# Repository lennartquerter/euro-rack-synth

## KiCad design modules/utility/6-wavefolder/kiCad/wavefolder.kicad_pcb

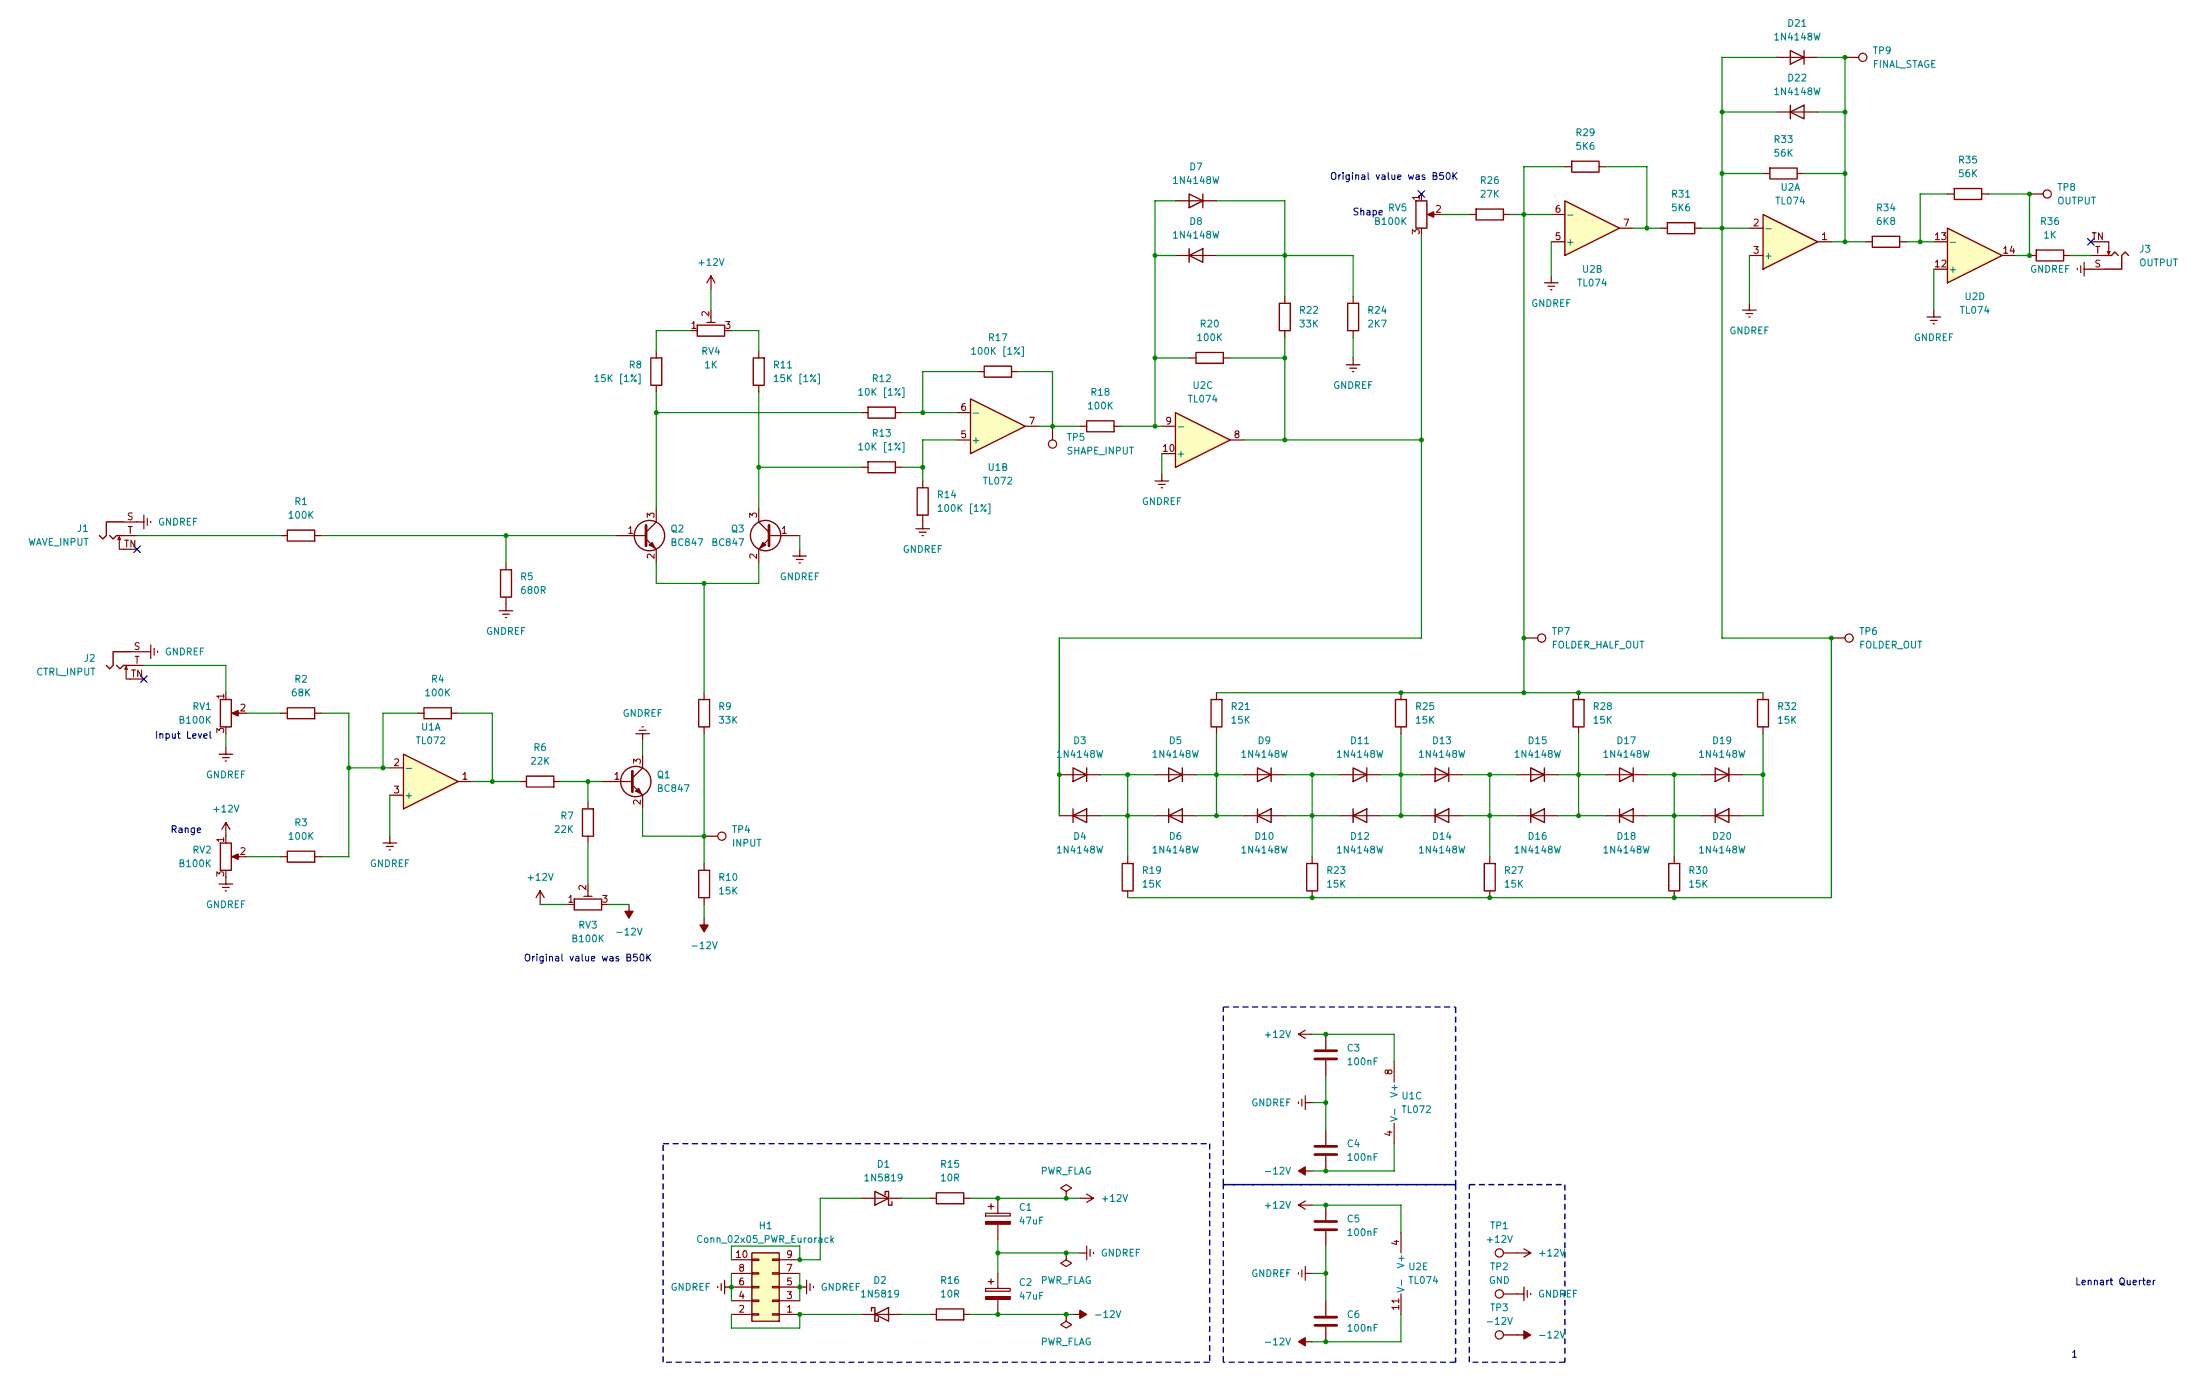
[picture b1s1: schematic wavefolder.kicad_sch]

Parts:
C1, C2: 47uF; CP_Radial_D6.3mm_P2.50mm
C3, C4, C5, C6: 100nF; C_0805_2012Metric_Pad1.18x1.45mm_HandSolder
D1, D2: 1N5819; D_SOD-123
D3, D4, D5, D6, D7, D8, D9, D10, D11, D12, D13, D14, D15, D16, D17, D18, D19, D20, D21, D22: 1N4148W; D_SOD-123
H1: Conn_02x05_PWR_Eurorack; IDC-Header_2x05_P2.54mm_Vertical
J1: WAVE_INPUT; Jack_3.5mm_QingPu_WQP-PJ398SM_Vertical_CircularHoles
J2: CTRL_INPUT; Jack_3.5mm_QingPu_WQP-PJ398SM_Vertical_CircularHoles
J3: OUTPUT; Jack_3.5mm_QingPu_WQP-PJ398SM_Vertical_CircularHoles
Q1, Q2, Q3: BC847; SOT-23
R1, R3, R4, R18, R20: 100K; R_0805_2012Metric_Pad1.20x1.40mm_HandSolder
R2: 68K; R_0805_2012Metric_Pad1.20x1.40mm_HandSolder
R5: 680R; R_0805_2012Metric_Pad1.20x1.40mm_HandSolder
R6, R7: 22K; R_0805_2012Metric_Pad1.20x1.40mm_HandSolder
R8, R11: 15K [1%]; R_0805_2012Metric_Pad1.20x1.40mm_HandSolder
R9, R22: 33K; R_0805_2012Metric_Pad1.20x1.40mm_HandSolder
R10, R19, R21, R23, R25, R27, R28, R30, R32: 15K; R_0805_2012Metric_Pad1.20x1.40mm_HandSolder
R12, R13: 10K [1%]; R_0805_2012Metric_Pad1.20x1.40mm_HandSolder
R14, R17: 100K [1%]; R_0805_2012Metric_Pad1.20x1.40mm_HandSolder
R15, R16: 10R; R_0805_2012Metric_Pad1.20x1.40mm_HandSolder
R24: 2K7; R_0805_2012Metric_Pad1.20x1.40mm_HandSolder
R26: 27K; R_0805_2012Metric_Pad1.20x1.40mm_HandSolder
R29, R31: 5K6; R_0805_2012Metric_Pad1.20x1.40mm_HandSolder
R33, R35: 56K; R_0805_2012Metric_Pad1.20x1.40mm_HandSolder
R34: 6K8; R_0805_2012Metric_Pad1.20x1.40mm_HandSolder
R36: 1K; R_0805_2012Metric_Pad1.20x1.40mm_HandSolder
RV1, RV2, RV5: B100K; Potentiometer_TT_P0915N
RV3: B100K; Potentiometer_Bourns_3296W_Vertical
RV4: 1K; Potentiometer_Bourns_3296W_Vertical
TP1: +12V; Pin_D1.0mm_L10.0mm
TP2: GND; Pin_D1.0mm_L10.0mm
TP3: -12V; Pin_D1.0mm_L10.0mm
TP4: INPUT; Pin_D1.0mm_L10.0mm
TP5: SHAPE_INPUT; Pin_D1.0mm_L10.0mm
TP6: FOLDER_OUT; Pin_D1.0mm_L10.0mm
TP7: FOLDER_HALF_OUT; Pin_D1.0mm_L10.0mm
TP8: OUTPUT; Pin_D1.0mm_L10.0mm
TP9: FINAL_STAGE; Pin_D1.0mm_L10.0mm
U1: TL072; SO-8_3.9x4.9mm_P1.27mm
U2: TL074; SO-14_3.9x8.65mm_P1.27mm

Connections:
+12V: C1.1, C3.1, C5.1, R15.2, RV2.1, RV3.1, RV4.2, TP1.1, U1.8 (V+), U2.4 (V+)
-12V: C2.2, C4.2, C6.2, R10.1, R16.2, RV3.3, TP3.1, U1.4 (V-), U2.11 (V-)
GNDREF: C1.2, C2.1, C3.2, C4.1, C5.2, C6.1, H1.3, H1.4, H1.5, H1.6, H1.7, H1.8, J1.S, J2.S, J3.S, Q1.3 (C), Q3.1 (B), R5.1, R14.2, R24.1, RV1.3, RV2.3, TP2.1, U1.3 (+), U2.3 (+), U2.5 (+), U2.10 (+), U2.12 (+)
unnamed: D1.2 (A), H1.9, H1.10
unnamed: D1.1 (K), R15.1
unnamed: D2.2 (A), R16.1
unnamed: D2.1 (K), H1.1, H1.2
unnamed: D3.2 (A), D4.1 (K), R20.2, R22.1, RV5.3, U2.8
unnamed: D3.1 (K), D4.2 (A), D5.2 (A), D6.1 (K), R19.2
unnamed: D7.2 (A), D8.1 (K), R18.2, R20.1, U2.9 (-)
unnamed: D7.1 (K), D8.2 (A), R22.2, R24.2
unnamed: D9.1 (K), D10.2 (A), D11.2 (A), D12.1 (K), R23.2
unnamed: D5.1 (K), D6.2 (A), D9.2 (A), D10.1 (K), R21.1
unnamed: D11.1 (K), D12.2 (A), D13.2 (A), D14.1 (K), R25.1
unnamed: D13.1 (K), D14.2 (A), D15.2 (A), D16.1 (K), R27.2
unnamed: D15.1 (K), D16.2 (A), D17.2 (A), D18.1 (K), R28.1
unnamed: D17.1 (K), D18.2 (A), D19.2 (A), D20.1 (K), R30.2
unnamed: D19.1 (K), D20.2 (A), R32.1
unnamed: D21.2 (A), D22.1 (K), R19.1, R23.1, R27.1, R30.1, R31.1, R33.2, TP6.1, U2.2 (-)
unnamed: D21.1 (K), D22.2 (A), R33.1, R34.2, TP9.1, U2.1
unnamed: J1.T, R1.1
unnamed: J2.T, RV1.1
unnamed: J3.T, R36.1
unnamed: Q1.1 (B), R6.2, R7.2
unnamed: Q1.2 (E), R9.1, R10.2, TP4.1
unnamed: Q2.1 (B), R1.2, R5.2
unnamed: Q2.3 (C), R8.1, R12.2
unnamed: Q2.2 (E), Q3.2 (E), R9.2
unnamed: Q3.3 (C), R11.1, R13.2
unnamed: R2.1, RV1.2
unnamed: R3.1, RV2.2
unnamed: R4.2, R6.1, U1.1
unnamed: R7.1, RV3.2
unnamed: R8.2, RV4.1
unnamed: R11.2, RV4.3
unnamed: R17.2, R18.1, TP5.1, U1.7
unnamed: R26.2, RV5.2
unnamed: R29.1, R31.2, U2.7
unnamed: R35.1, R36.2, TP8.1, U2.14
unnamed: R2.2, R3.2, R4.1, U1.2 (-)
unnamed: R13.1, R14.1, U1.5 (+)
unnamed: R12.1, R17.1, U1.6 (-)
unnamed: R21.2, R25.2, R26.1, R28.2, R29.2, R32.2, TP7.1, U2.6 (-)
unnamed: R34.1, R35.2, U2.13 (-)

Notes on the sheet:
Original value was B50K
Range
Shape
Lennart Querter
Input Level

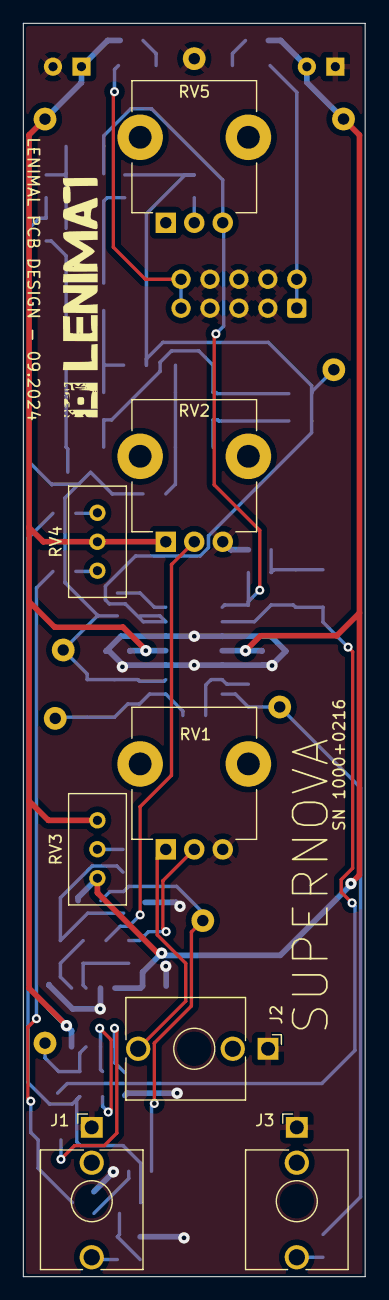
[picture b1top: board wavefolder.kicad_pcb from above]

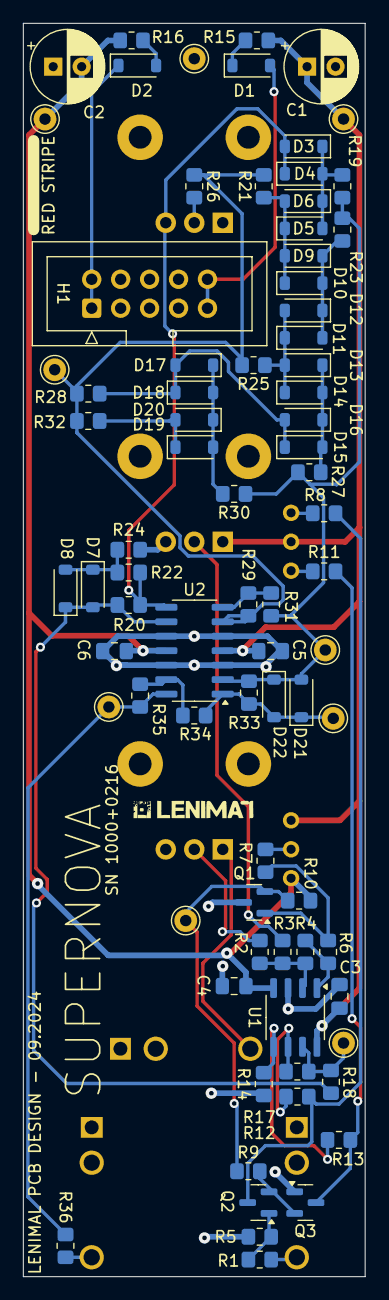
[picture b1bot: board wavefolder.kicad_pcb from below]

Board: 2 copper layers, 30.0 x 110.0 mm, 87 parts (79 on the bottom side), 44 nets.

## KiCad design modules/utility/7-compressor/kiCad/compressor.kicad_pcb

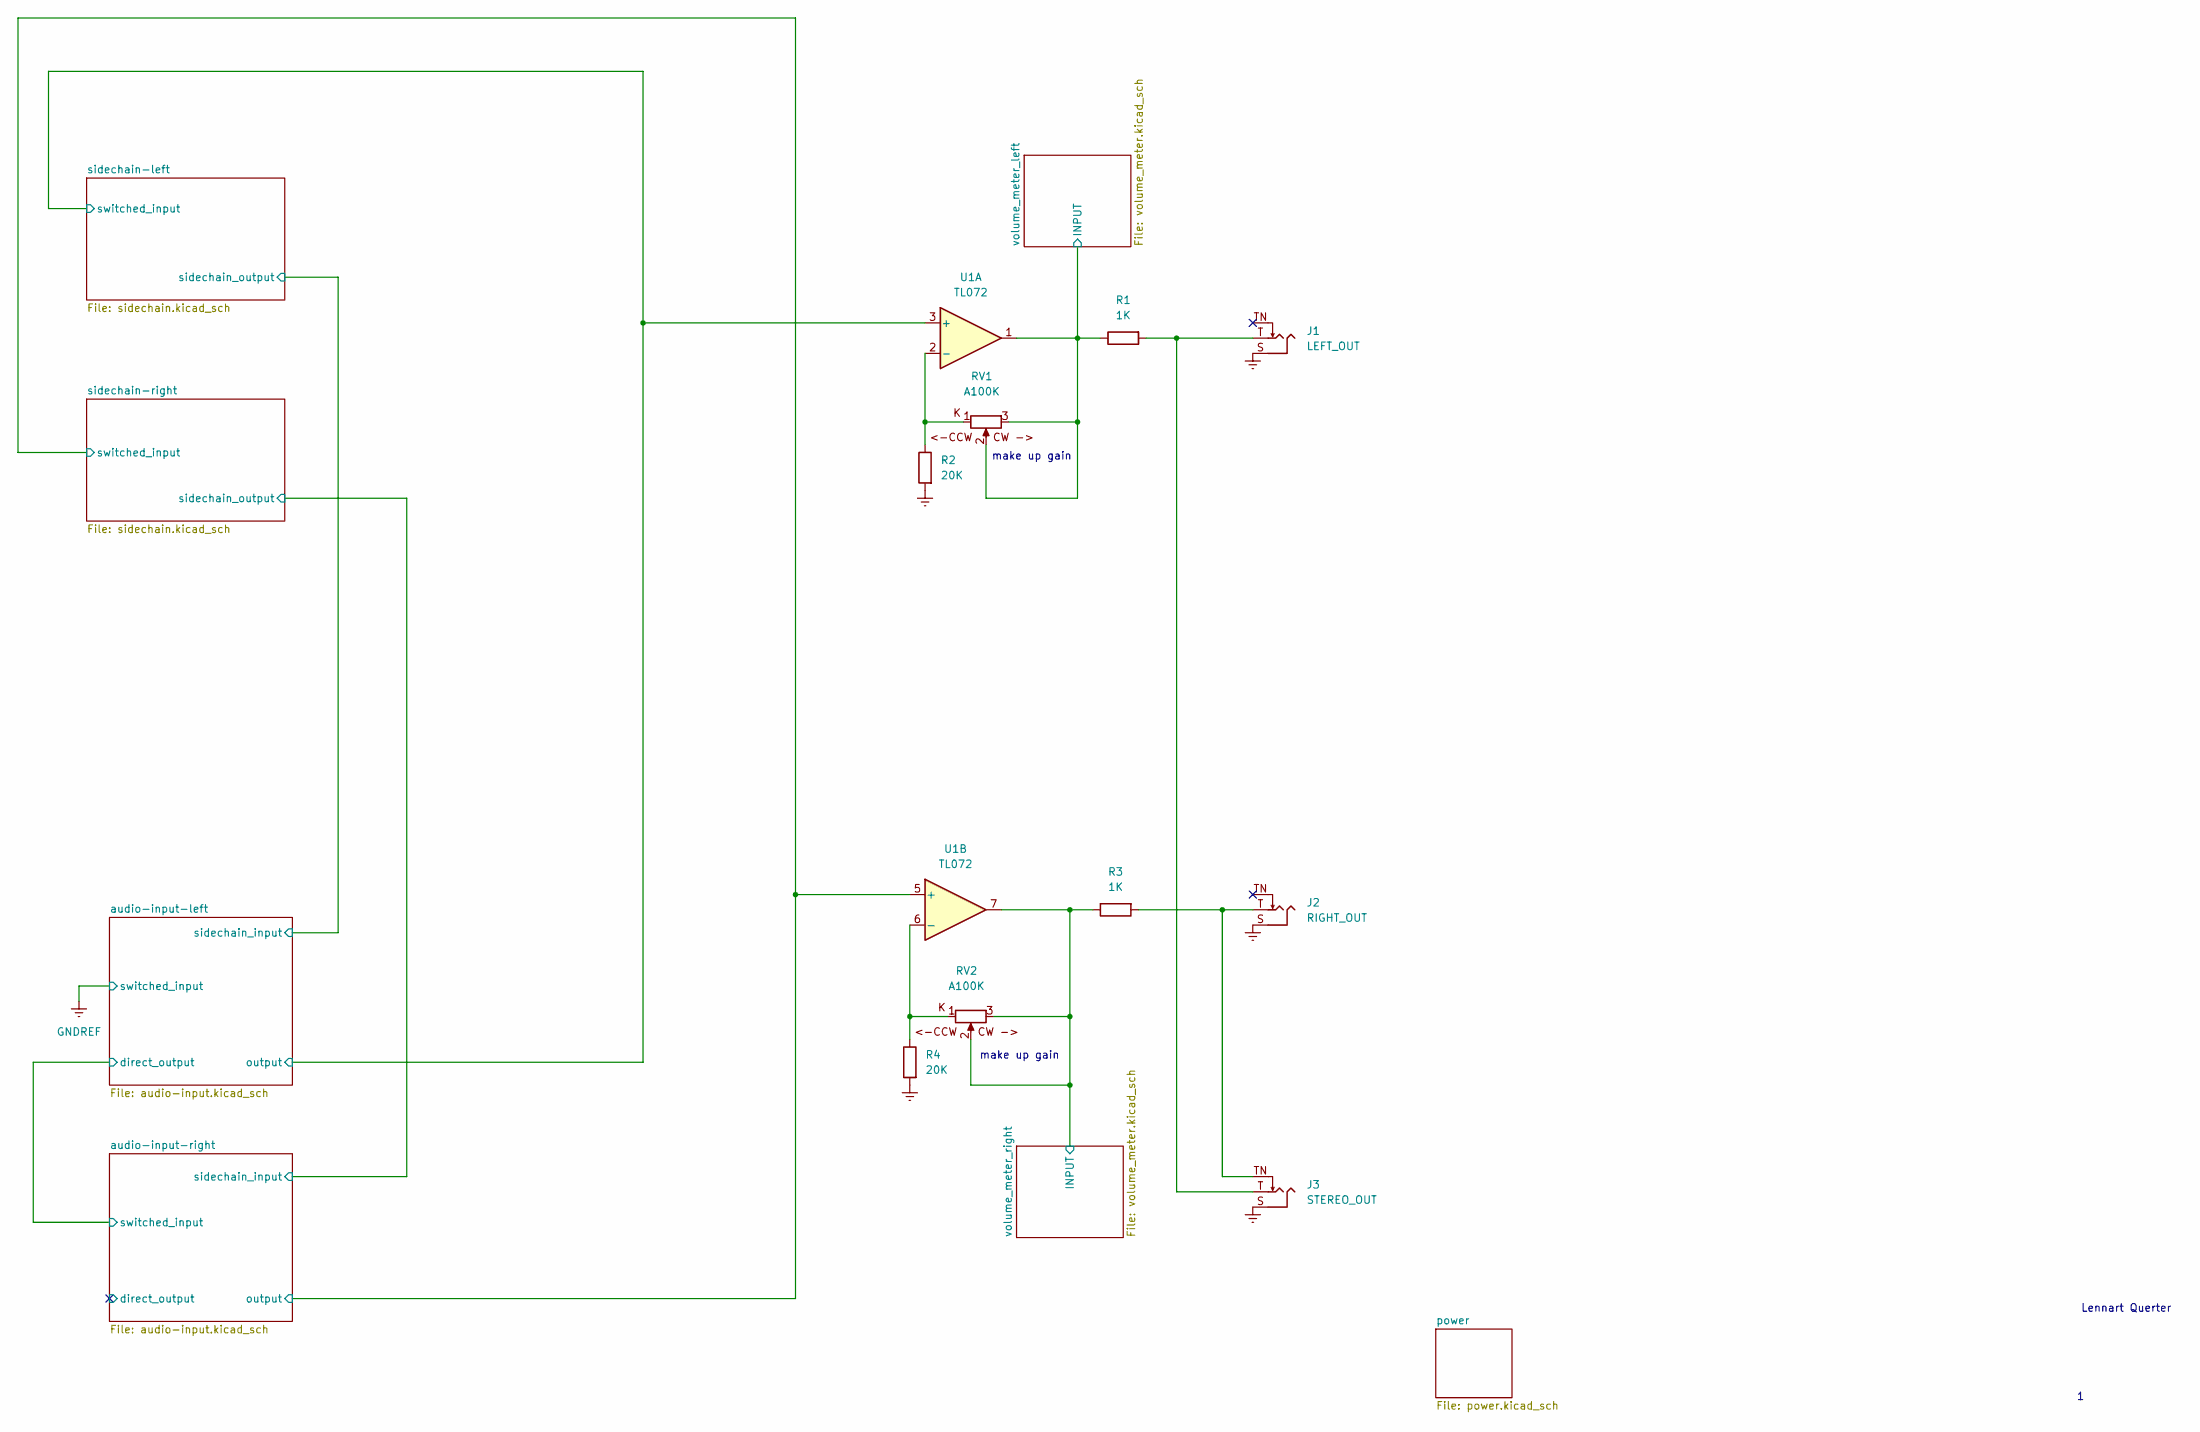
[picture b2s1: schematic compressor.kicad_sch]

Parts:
J1: LEFT_OUT; Jack_3.5mm_QingPu_WQP-PJ398SM_Vertical_CircularHoles
J2: RIGHT_OUT; Jack_3.5mm_QingPu_WQP-PJ398SM_Vertical_CircularHoles
J3: STEREO_OUT; Jack_3.5mm_QingPu_WQP-PJ398SM_Vertical_CircularHoles
R1, R3: 1K; R_0805_2012Metric_Pad1.20x1.40mm_HandSolder
R2, R4: 20K; R_0805_2012Metric_Pad1.20x1.40mm_HandSolder
RV1, RV2: A100K; Potentiometer_TT_P0915N
U1: TL072; SOIC-8

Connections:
/audio-input-left/output: U1.3 (+); also elsewhere on the board
/audio-input-right/output: U1.5 (+); also elsewhere on the board
/volume_meter_left/INPUT: R1.2, RV1.2, RV1.3, U1.1; also elsewhere on the board
/volume_meter_right/INPUT: R3.2, RV2.2, RV2.3, U1.7; also elsewhere on the board
GNDREF: J1.S, J2.S, J3.S, R2.1, R4.1; also elsewhere on the board
unnamed: J1.T, J3.T, R1.1
unnamed: J2.T, J3.TN, R3.1
unnamed: R2.2, RV1.1, U1.2 (-)
unnamed: R4.2, RV2.1, U1.6 (-)

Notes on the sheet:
make up gain
Lennart Querter

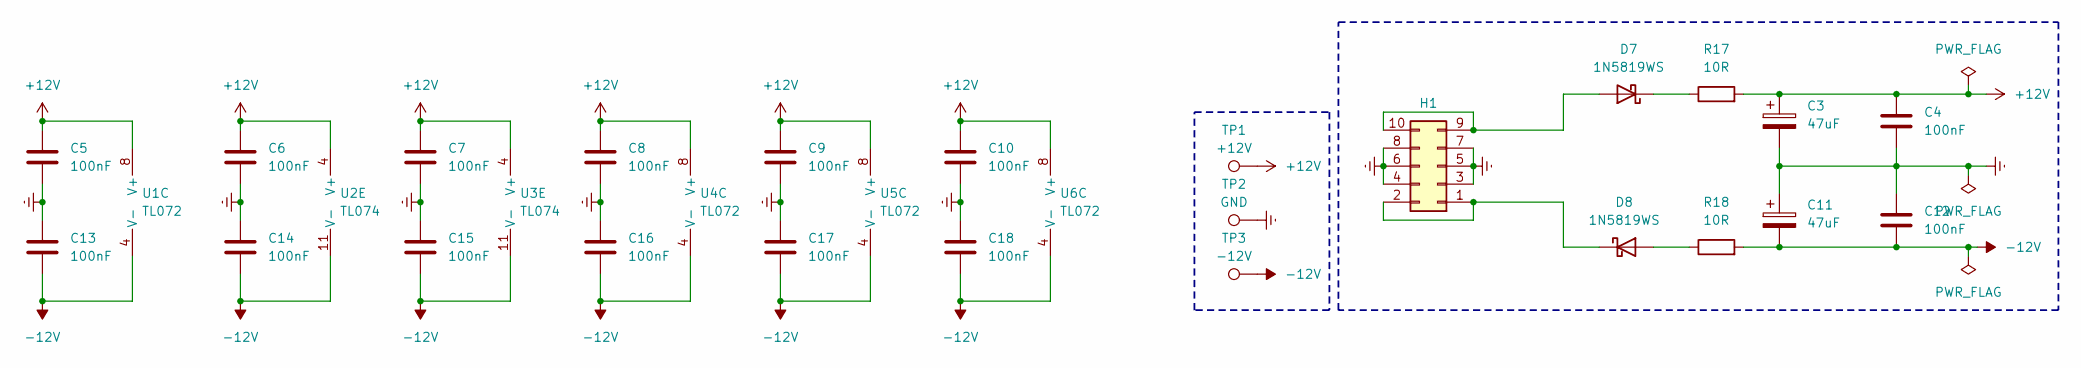
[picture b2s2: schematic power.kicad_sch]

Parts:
C3, C11: 47uF; CP_Radial_D6.3mm_P2.50mm
C4, C5, C6, C7, C8, C9, C10, C12, C13, C14, C15, C16, C17, C18: 100nF; C_0805_2012Metric_Pad1.18x1.45mm_HandSolder
D7, D8: 1N5819WS; D_SOD-323_HandSoldering
H1: Conn_02x05_PWR_Eurorack; IDC-Header_2x05_P2.54mm_Vertical
R17, R18: 10R; R_0805_2012Metric_Pad1.20x1.40mm_HandSolder
TP1: +12V; Pin_D1.0mm_L10.0mm
TP2: GND; Pin_D1.0mm_L10.0mm
TP3: -12V; Pin_D1.0mm_L10.0mm
U1, U4, U5, U6: TL072; SOIC-8
U2, U3: TL074; SOIC-14

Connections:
+12V: C3.1, C4.1, C5.1, C6.1, C7.1, C8.1, C9.1, C10.1, R17.2, TP1.1 (1_1), U1.8 (V+), U2.4 (V+), U3.4 (V+), U4.8 (V+), U5.8 (V+), U6.8 (V+); also elsewhere on the board
-12V: C11.2, C12.2, C13.2, C14.2, C15.2, C16.2, C17.2, C18.2, R18.2, TP3.1 (1_1), U1.4 (V-), U2.11 (V-), U3.11 (V-), U4.4 (V-), U5.4 (V-), U6.4 (V-)
/audio-input-left/output: U5.7; also elsewhere on the board
GNDREF: C3.2, C4.2, C5.2, C6.2, C7.2, C8.2, C9.2, C10.2, C11.1, C12.1, C13.1, C14.1, C15.1, C16.1, C17.1, C18.1, H1.3, H1.4, H1.5, H1.6, H1.7, H1.8, TP2.1 (1_1); also elsewhere on the board
unnamed: D7.2 (A), H1.9, H1.10
unnamed: D7.1 (K), R17.1
unnamed: D8.2 (A), R18.1
unnamed: D8.1 (K), H1.1, H1.2
unnamed 43: U5.5 (+); also elsewhere on the board
unnamed 113: U5.6 (-); also elsewhere on the board

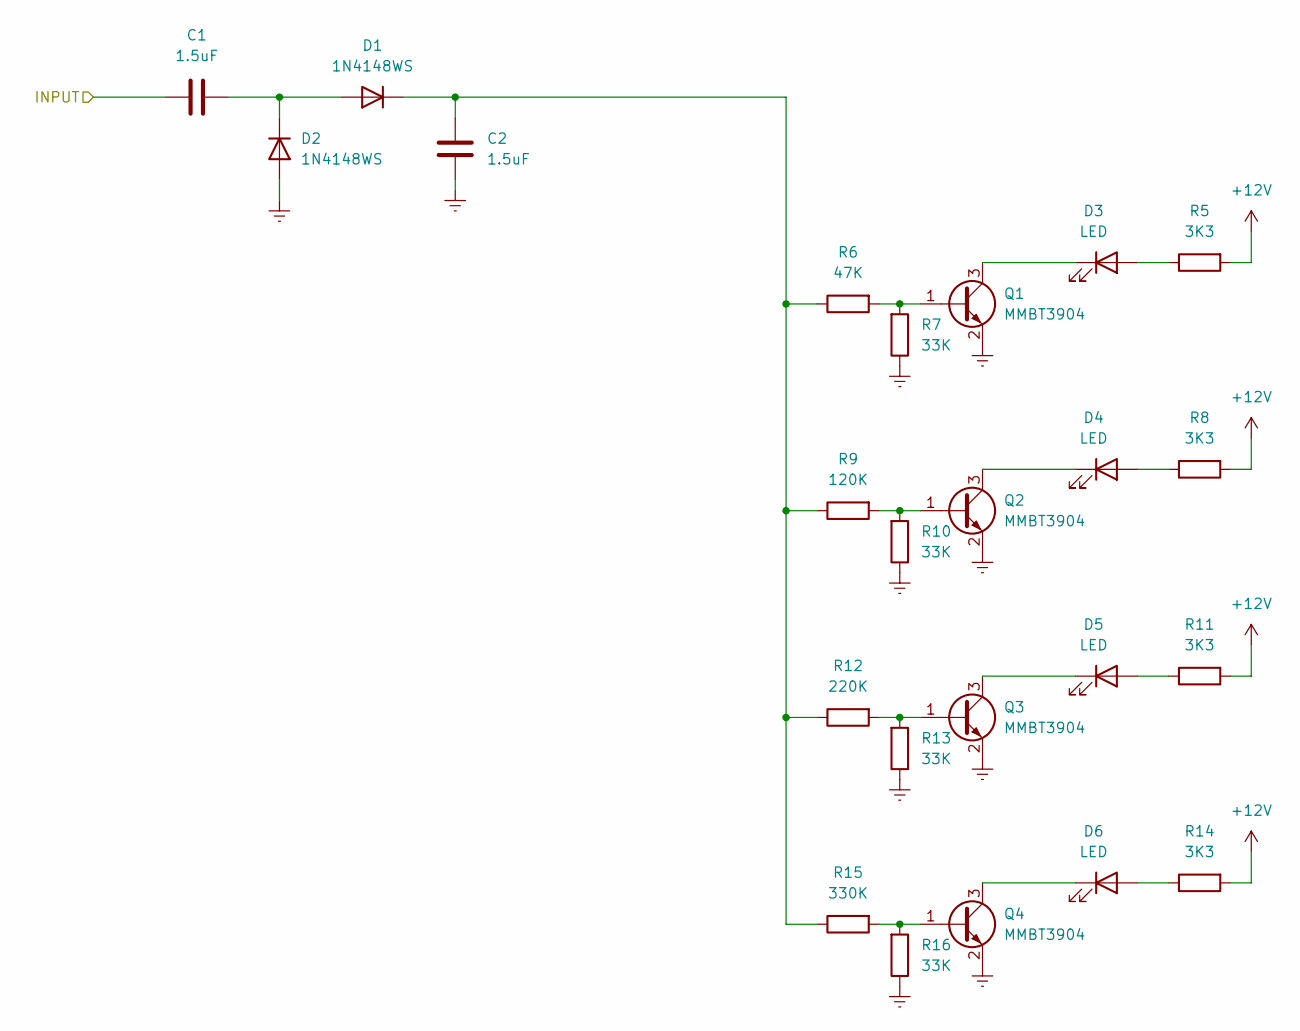
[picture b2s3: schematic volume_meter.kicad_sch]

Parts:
C1, C2: 1.5uF; C_0805_2012Metric_Pad1.18x1.45mm_HandSolder
D1, D2: 1N4148WS; D_SOD-323_HandSoldering
D3, D4, D5, D6: LED; LED_D3.0mm
Q1, Q2, Q3, Q4: MMBT3904; SOT-23_Handsoldering
R5, R8, R11, R14: 3K3; R_0805_2012Metric_Pad1.20x1.40mm_HandSolder
R6: 47K; R_0805_2012Metric_Pad1.20x1.40mm_HandSolder
R7, R10, R13, R16: 33K; R_0805_2012Metric_Pad1.20x1.40mm_HandSolder
R9: 120K; R_0805_2012Metric_Pad1.20x1.40mm_HandSolder
R12: 220K; R_0805_2012Metric_Pad1.20x1.40mm_HandSolder
R15: 330K; R_0805_2012Metric_Pad1.20x1.40mm_HandSolder

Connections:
+12V: R5.1, R8.1, R11.1, R14.1; also elsewhere on the board
/volume_meter_right/INPUT: C1.1; also elsewhere on the board
GNDREF: C2.1, D2.2 (A), Q1.2 (E), Q2.2 (E), Q3.2 (E), Q4.2 (E), R7.2, R10.2, R13.2, R16.2; also elsewhere on the board
unnamed: C1.2, D1.2 (A), D2.1 (K)
unnamed: C2.2, D1.1 (K), R6.2, R9.2, R12.2, R15.2
unnamed: D3.2 (A), R5.2
unnamed: D3.1 (K), Q1.3 (C)
unnamed: D4.2 (A), R8.2
unnamed: D4.1 (K), Q2.3 (C)
unnamed: D5.2 (A), R11.2
unnamed: D5.1 (K), Q3.3 (C)
unnamed: D6.2 (A), R14.2
unnamed: D6.1 (K), Q4.3 (C)
unnamed: Q1.1 (B), R6.1, R7.1
unnamed: Q2.1 (B), R9.1, R10.1
unnamed: Q3.1 (B), R12.1, R13.1
unnamed: Q4.1 (B), R15.1, R16.1

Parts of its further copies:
C19, C20: 1.5uF; C_0805_2012Metric_Pad1.18x1.45mm_HandSolder
D9, D10: 1N4148WS; D_SOD-323_HandSoldering
D11, D12, D13, D14: LED; LED_D3.0mm
Q5, Q6, Q7, Q8: MMBT3904; SOT-23_Handsoldering
R19, R22, R25, R28: 3K3; R_0805_2012Metric_Pad1.20x1.40mm_HandSolder
R20: 47K; R_0805_2012Metric_Pad1.20x1.40mm_HandSolder
R21, R24, R27, R30: 33K; R_0805_2012Metric_Pad1.20x1.40mm_HandSolder
R23: 120K; R_0805_2012Metric_Pad1.20x1.40mm_HandSolder
R26: 220K; R_0805_2012Metric_Pad1.20x1.40mm_HandSolder
R29: 330K; R_0805_2012Metric_Pad1.20x1.40mm_HandSolder

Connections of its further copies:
+12V: R19.1, R22.1, R25.1, R28.1; also elsewhere on the board
/volume_meter_left/INPUT: C19.1; also elsewhere on the board
GNDREF: C20.1, D10.2 (A), Q5.2 (E), Q6.2 (E), Q7.2 (E), Q8.2 (E), R21.2, R24.2, R27.2, R30.2; also elsewhere on the board
unnamed: C20.2, D9.1 (K), R20.2, R23.2, R26.2, R29.2
unnamed: C19.2, D9.2 (A), D10.1 (K)
unnamed: D11.2 (A), R19.2
unnamed: D11.1 (K), Q5.3 (C)
unnamed: D12.2 (A), R22.2
unnamed: D12.1 (K), Q6.3 (C)
unnamed: D13.2 (A), R25.2
unnamed: D13.1 (K), Q7.3 (C)
unnamed: D14.2 (A), R28.2
unnamed: D14.1 (K), Q8.3 (C)
unnamed: Q5.1 (B), R20.1, R21.1
unnamed: Q6.1 (B), R23.1, R24.1
unnamed: Q7.1 (B), R26.1, R27.1
unnamed: Q8.1 (B), R29.1, R30.1

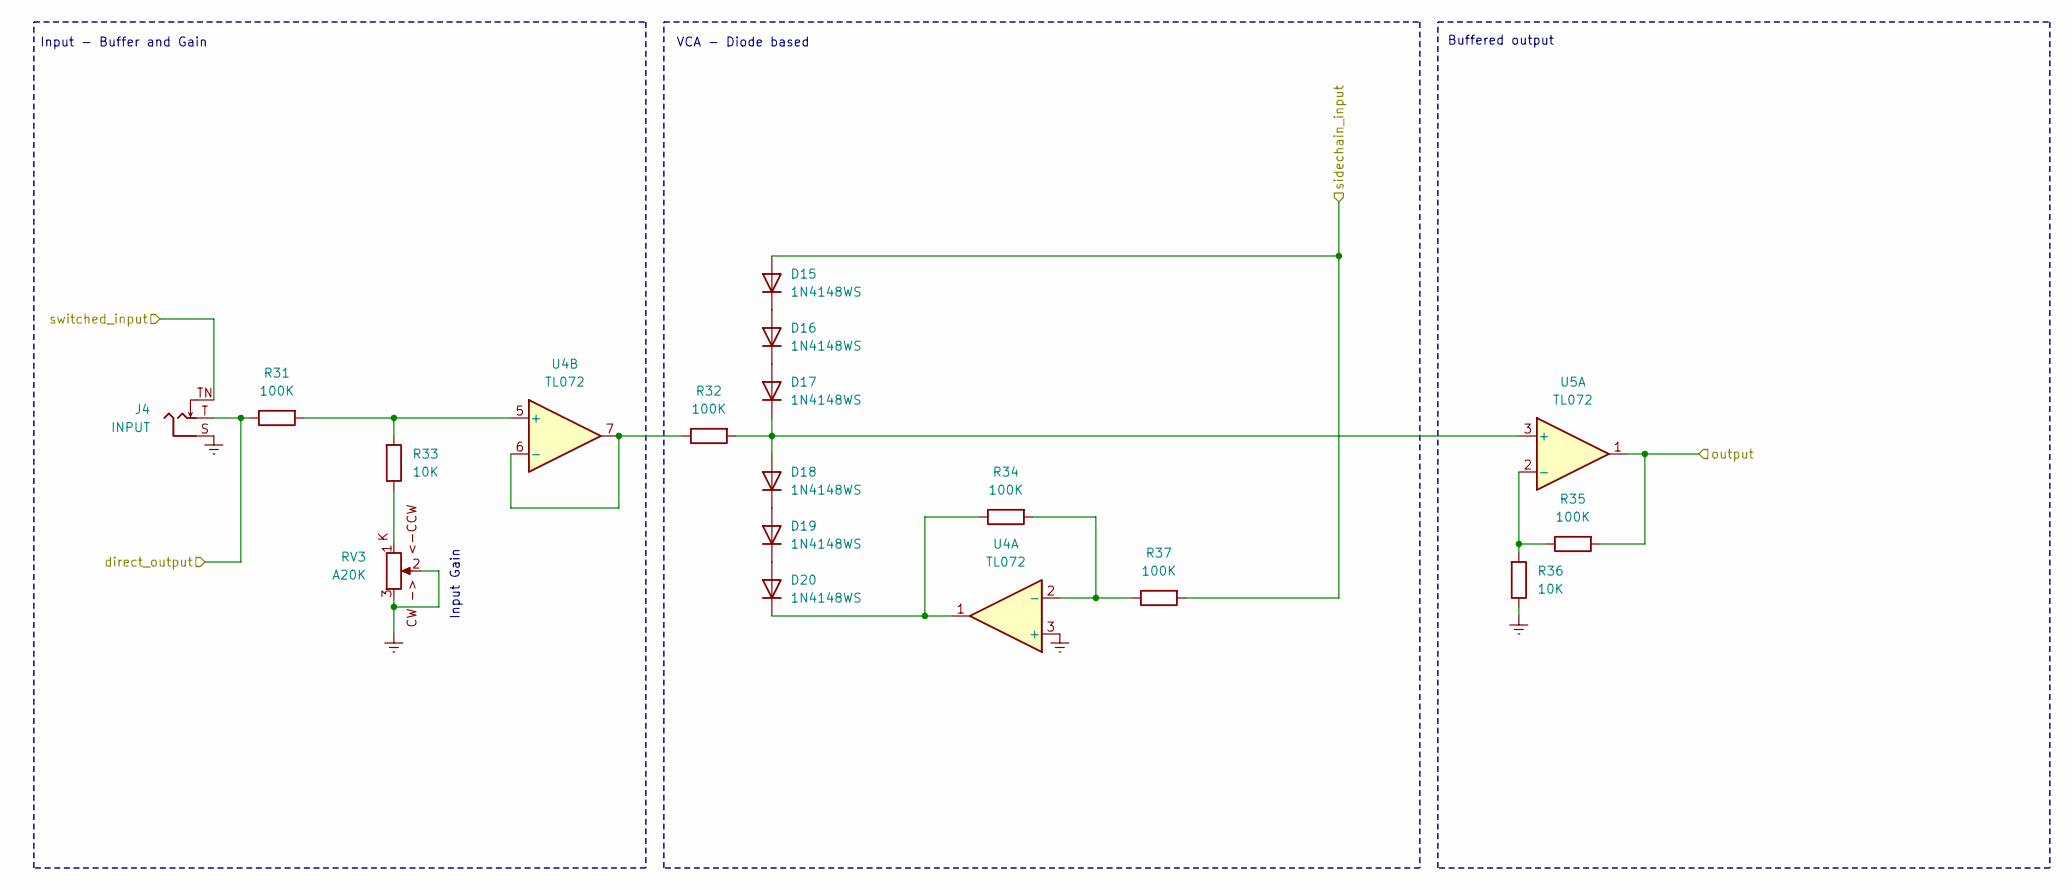
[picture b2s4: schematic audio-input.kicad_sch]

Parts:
D15, D16, D17, D18, D19, D20: 1N4148WS; D_SOD-323_HandSoldering
J4: INPUT; Jack_3.5mm_QingPu_WQP-PJ398SM_Vertical_CircularHoles
R31, R32, R34, R35, R37: 100K; R_0805_2012Metric_Pad1.20x1.40mm_HandSolder
R33, R36: 10K; R_0805_2012Metric_Pad1.20x1.40mm_HandSolder
RV3: A20K; Potentiometer_TT_P0915N
U4, U5: TL072; SOIC-8

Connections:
/audio-input-left/direct_output: J4.TN; also elsewhere on the board
/audio-input-left/output: U5.7; also elsewhere on the board
/audio-input-right/direct_output: J4.T, R31.2
/audio-input-right/output: R35.1, U5.1; also elsewhere on the board
/audio-input-right/sidechain_input: D15.2 (A), R37.1; also elsewhere on the board
GNDREF: J4.S, R36.2, RV3.2, RV3.3, U4.3 (+); also elsewhere on the board
unnamed: D15.1 (K), D16.2 (A)
unnamed: D16.1 (K), D17.2 (A)
unnamed: D17.1 (K), D18.2 (A), R32.1, U5.3 (+)
unnamed: D18.1 (K), D19.2 (A)
unnamed: D19.1 (K), D20.2 (A)
unnamed: D20.1 (K), R34.2, U4.1
unnamed 43: U5.5 (+); also elsewhere on the board
unnamed: R33.2, RV3.1
unnamed: R34.1, R37.2, U4.2 (-)
unnamed: R31.1, R33.1, U4.5 (+)
unnamed: R32.2, U4.6 (-), U4.7
unnamed: R35.2, R36.1, U5.2 (-)
unnamed 113: U5.6 (-); also elsewhere on the board

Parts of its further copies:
D21, D22, D23, D24, D25, D26: 1N4148WS; D_SOD-323_HandSoldering
J5: INPUT; Jack_3.5mm_QingPu_WQP-PJ398SM_Vertical_CircularHoles
R38, R39, R41, R42, R44: 100K; R_0805_2012Metric_Pad1.20x1.40mm_HandSolder
R40, R43: 10K; R_0805_2012Metric_Pad1.20x1.40mm_HandSolder
RV4: A20K; Potentiometer_TT_P0915N

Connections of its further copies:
/audio-input-left/direct_output: J5.T, R38.2; also elsewhere on the board
/audio-input-left/output: R42.1; also elsewhere on the board
/audio-input-left/sidechain_input: D21.2 (A), R44.1; also elsewhere on the board
GNDREF: J5.S, J5.TN, R43.2, RV4.2, RV4.3; also elsewhere on the board
unnamed: D21.1 (K), D22.2 (A)
unnamed: D22.1 (K), D23.2 (A)
unnamed 43: D23.1 (K), D24.2 (A), R39.1; also elsewhere on the board
unnamed: D24.1 (K), D25.2 (A)
unnamed: D25.1 (K), D26.2 (A)
unnamed 46: D26.1 (K), R41.2; also elsewhere on the board
unnamed: R40.2, RV4.1
unnamed 113: R42.2, R43.1; also elsewhere on the board
unnamed 114: R41.1, R44.2; also elsewhere on the board
unnamed 115: R38.1, R40.1; also elsewhere on the board
unnamed 116: R39.2; also elsewhere on the board

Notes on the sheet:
Input Gain
Input - Buffer and Gain
Buffered output
VCA - Diode based

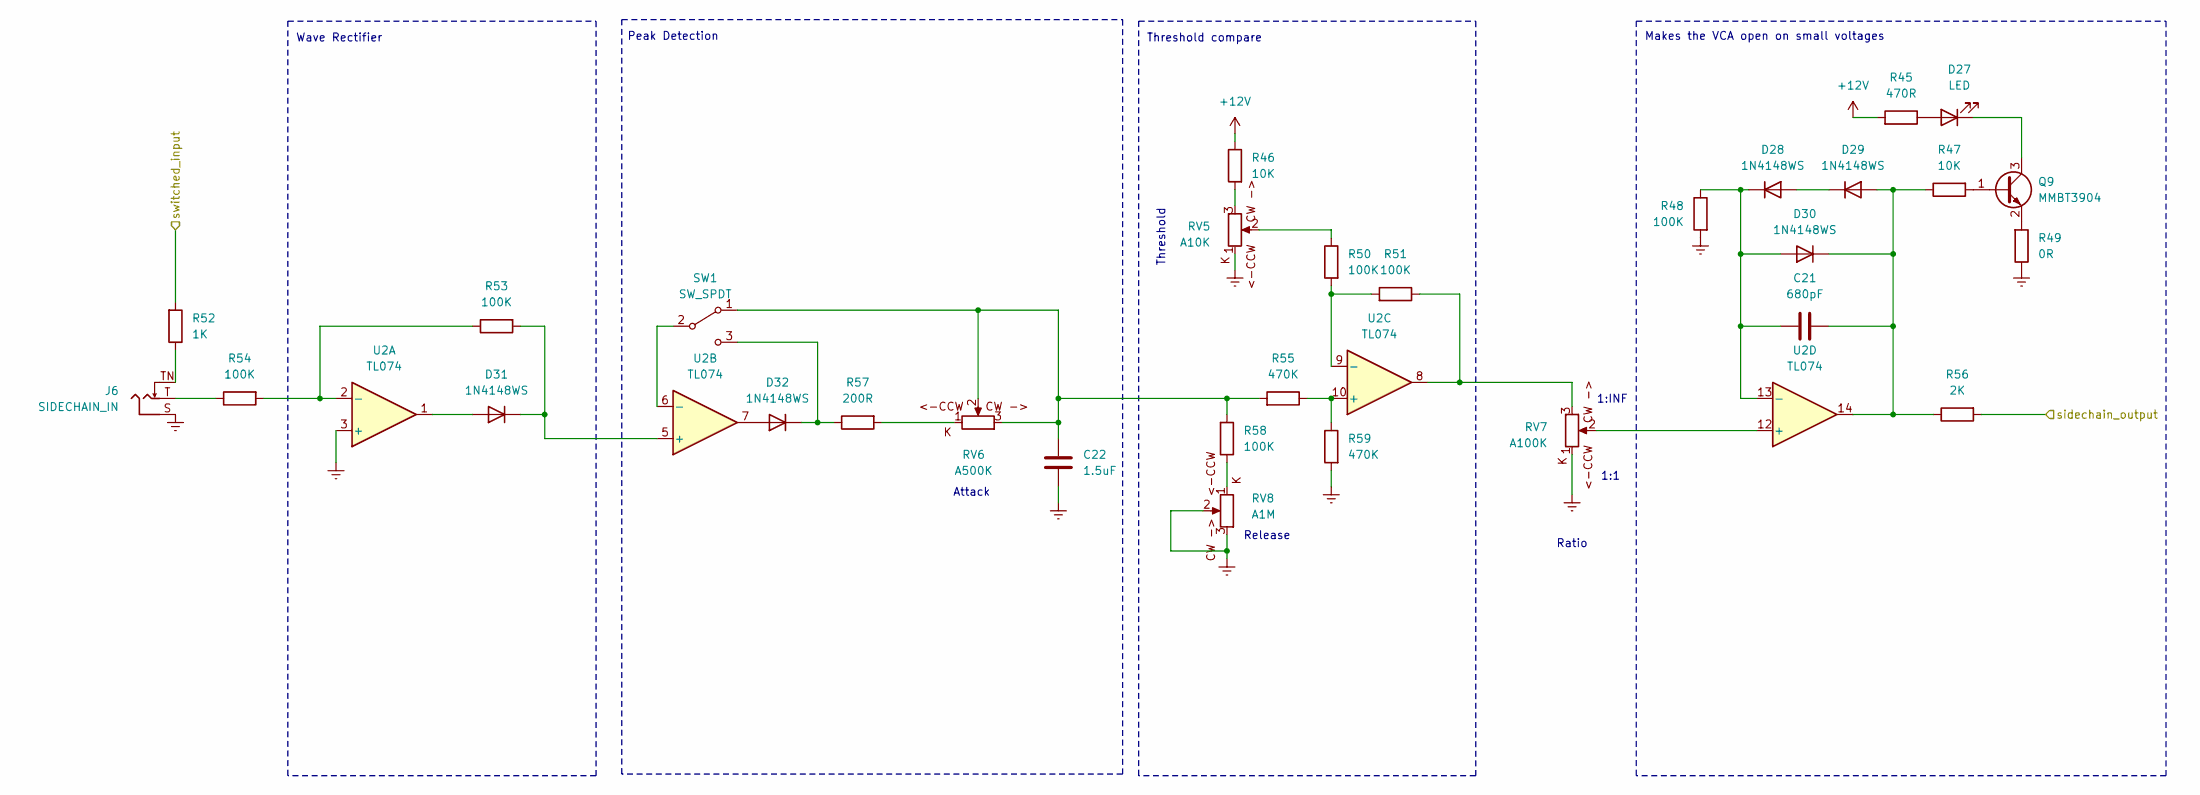
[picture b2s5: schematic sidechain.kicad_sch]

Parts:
C21: 680pF; C_0805_2012Metric_Pad1.18x1.45mm_HandSolder
C22: 1.5uF; C_0805_2012Metric_Pad1.18x1.45mm_HandSolder
D27: LED; LED_D3.0mm
D28, D29, D30, D31, D32: 1N4148WS; D_SOD-323_HandSoldering
J6: SIDECHAIN_IN; Jack_3.5mm_QingPu_WQP-PJ398SM_Vertical_CircularHoles
Q9: MMBT3904; SOT-23_Handsoldering
R45: 470R; R_0805_2012Metric_Pad1.20x1.40mm_HandSolder
R46, R47: 10K; R_0805_2012Metric_Pad1.20x1.40mm_HandSolder
R48, R50, R51, R53, R54, R58: 100K; R_0805_2012Metric_Pad1.20x1.40mm_HandSolder
R49: 0R; R_0805_2012Metric_Pad1.20x1.40mm_HandSolder
R52: 1K; R_0805_2012Metric_Pad1.20x1.40mm_HandSolder
R55, R59: 470K; R_0805_2012Metric_Pad1.20x1.40mm_HandSolder
R56: 2K; R_0805_2012Metric_Pad1.20x1.40mm_HandSolder
R57: 200R; R_0805_2012Metric_Pad1.20x1.40mm_HandSolder
RV5: A10K; Potentiometer_TT_P0915N
RV6: A500K; Potentiometer_TT_P0915N
RV7: A100K; Potentiometer_TT_P0915N
RV8: A1M; Potentiometer_TT_P0915N
SW1: SW_SPDT; SW_default
U2: TL074; SOIC-14

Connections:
+12V: R45.1, R46.2; also elsewhere on the board
/audio-input-right/output: R52.1; also elsewhere on the board
/audio-input-right/sidechain_input: R56.1; also elsewhere on the board
GNDREF: C22.1, J6.S, R48.1, R49.2, R59.1, RV5.1, RV7.1, RV8.2, RV8.3, U2.3 (+); also elsewhere on the board
unnamed: D27.2 (A), R45.2
unnamed: D27.1 (K), Q9.3 (C)
unnamed: D28.2 (A), D29.1 (K)
unnamed: C21.2, D28.1 (K), D30.2 (A), R48.2, U2.13 (-)
unnamed: C21.1, D29.2 (A), D30.1 (K), R47.2, R56.2, U2.14
unnamed: D31.2 (A), U2.1
unnamed: D31.1 (K), R53.1, U2.5 (+)
unnamed: D32.2 (A), U2.7
unnamed: D32.1 (K), R57.2, SW1.3 (C)
unnamed: J6.T, R54.2
unnamed: J6.TN, R52.2
unnamed: Q9.1 (B), R47.1
unnamed: Q9.2 (E), R49.1
unnamed: R46.1, RV5.3
unnamed: R50.2, RV5.2
unnamed: R51.2, RV7.3, U2.8
unnamed: R57.1, RV6.1
unnamed: R58.2, RV8.1
unnamed: C22.2, R55.1, R58.1, RV6.2, RV6.3, SW1.1 (A)
unnamed: SW1.2 (B), U2.6 (-)
unnamed: R53.2, R54.1, U2.2 (-)
unnamed: R55.2, R59.2, U2.10 (+)
unnamed: R50.1, R51.1, U2.9 (-)
unnamed: RV7.2, U2.12 (+)

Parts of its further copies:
C23: 680pF; C_0805_2012Metric_Pad1.18x1.45mm_HandSolder
C24: 1.5uF; C_0805_2012Metric_Pad1.18x1.45mm_HandSolder
D33: LED; LED_D3.0mm
D34, D35, D36, D37, D38: 1N4148WS; D_SOD-323_HandSoldering
J7: SIDECHAIN_IN; Jack_3.5mm_QingPu_WQP-PJ398SM_Vertical_CircularHoles
Q10: MMBT3904; SOT-23_Handsoldering
R60: 470R; R_0805_2012Metric_Pad1.20x1.40mm_HandSolder
R61, R62: 10K; R_0805_2012Metric_Pad1.20x1.40mm_HandSolder
R63, R65, R66, R68, R69, R73: 100K; R_0805_2012Metric_Pad1.20x1.40mm_HandSolder
R64: 0R; R_0805_2012Metric_Pad1.20x1.40mm_HandSolder
R67: 1K; R_0805_2012Metric_Pad1.20x1.40mm_HandSolder
R70, R74: 470K; R_0805_2012Metric_Pad1.20x1.40mm_HandSolder
R71: 2K; R_0805_2012Metric_Pad1.20x1.40mm_HandSolder
R72: 200R; R_0805_2012Metric_Pad1.20x1.40mm_HandSolder
RV9: A10K; Potentiometer_TT_P0915N
RV10: A500K; Potentiometer_TT_P0915N
RV11: A100K; Potentiometer_TT_P0915N
RV12: A1M; Potentiometer_TT_P0915N
SW2: SW_SPDT; SW_default

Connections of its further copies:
+12V: R60.1, R61.2; also elsewhere on the board
/audio-input-left/output: R67.1; also elsewhere on the board
/audio-input-left/sidechain_input: R71.1; also elsewhere on the board
GNDREF: C24.1, J7.S, R63.1, R64.2, R74.1, RV9.1, RV11.1, RV12.2, RV12.3; also elsewhere on the board
unnamed: D33.2 (A), R60.2
unnamed: D33.1 (K), Q10.3 (C)
unnamed: D34.2 (A), D35.1 (K)
unnamed 59: C23.2, D34.1 (K), D36.2 (A), R63.2; also elsewhere on the board
unnamed 60: C23.1, D35.2 (A), D36.1 (K), R62.2, R71.2; also elsewhere on the board
unnamed 61: D37.2 (A); also elsewhere on the board
unnamed 62: D37.1 (K), R68.1; also elsewhere on the board
unnamed 63: D38.2 (A); also elsewhere on the board
unnamed: D38.1 (K), R72.2, SW2.3 (C)
unnamed: J7.T, R69.2
unnamed: J7.TN, R67.2
unnamed: Q10.1 (B), R62.1
unnamed: Q10.2 (E), R64.1
unnamed: R61.1, RV9.3
unnamed: R65.2, RV9.2
unnamed 92: R66.2, RV11.3; also elsewhere on the board
unnamed: R72.1, RV10.1
unnamed: R73.2, RV12.1
unnamed: C24.2, R70.1, R73.1, RV10.2, RV10.3, SW2.1 (A)
unnamed 98: SW2.2 (B); also elsewhere on the board
unnamed 105: R68.2, R69.1; also elsewhere on the board
unnamed 106: R70.2, R74.2; also elsewhere on the board
unnamed 107: R65.1, R66.1; also elsewhere on the board
unnamed 108: RV11.2; also elsewhere on the board

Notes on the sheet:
Peak Detection
Threshold compare
Ratio
Attack
1:INF
Makes the VCA open on small voltages
Release
1:1
Threshold
Wave Rectifier
